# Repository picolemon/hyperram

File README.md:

# HyperRAM PMOD :lemon: # 

### Overview :hammer:
HyperRam board for use with PMOD compatible FPGA devices. This repo contains the
example RTL code, datasheets and schematics for the device.

### Whats included :musical_note:
- [x] Example wishbone memory controller.
- [x] Memory tester to validate the device works.
- [x] [Schematic](doc/sch.pdf), [PCB](pcb/) and [BOM](https://htmlpreview.github.io/?https://github.com/picolemon/hyperram/blob/main/doc/ibom.html).

### Getting started :mag:
Read the [datasheet](doc/datasheet.pdf) and run the [example](examples/) project.

### Support :zap:
- Drop by the [discord](https://discord.gg/Be3yFCzyrp)
- Email help@picolemon.com

### License :penguin:
 
The MIT License (MIT)

Copyright (c) 2023 picoLemon

Permission is hereby granted, free of charge, to any person obtaining a copy of this software and associated documentation files (the "Software"), to deal in the Software without restriction, including without limitation the rights to use, copy, modify, merge, publish, distribute, sublicense, and/or sell copies of the Software, and to permit persons to whom the Software is furnished to do so, subject to the following conditions:

The above copyright notice and this permission notice shall be included in all copies or substantial portions of the Software.

THE SOFTWARE IS PROVIDED "AS IS", WITHOUT WARRANTY OF ANY KIND, EXPRESS OR IMPLIED, INCLUDING BUT NOT LIMITED TO THE WARRANTIES OF MERCHANTABILITY, FITNESS FOR A PARTICULAR PURPOSE AND NONINFRINGEMENT. IN NO EVENT SHALL THE AUTHORS OR COPYRIGHT HOLDERS BE LIABLE FOR ANY CLAIM, DAMAGES OR OTHER LIABILITY, WHETHER IN AN ACTION OF CONTRACT, TORT OR OTHERWISE, ARISING FROM, OUT OF OR IN CONNECTION WITH THE SOFTWARE OR THE USE OR OTHER DEALINGS IN THE SOFTWARE.

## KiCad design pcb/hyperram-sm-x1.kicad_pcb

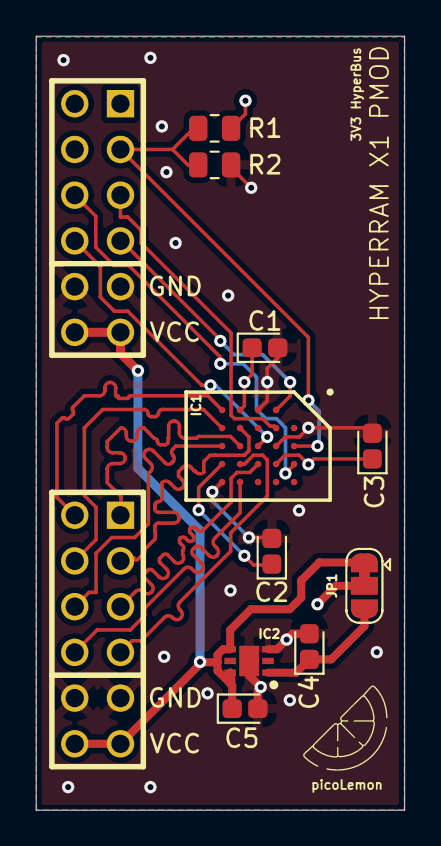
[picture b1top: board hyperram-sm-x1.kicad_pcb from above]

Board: 4 copper layers, 20.5 x 43.0 mm, 12 parts (0 on the bottom side), 17 nets.

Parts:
C1, C2, C3: 100n; CP_EIA-1608-08_AVX-J
C4, C5: 1u; CP_EIA-1608-08_AVX-J
IC1: W957A8MFYA5I; BGA24C100P5X5_600X800X120
IC2: NCP705MT18TCG; SON65P200X200X80-7N
J1, J2: PMOD; pmod_pin_array_6x2
JP1: VCC_3V_SEL; SolderJumper-3_P1.3mm_Bridged23_RoundedPad1.0x1.5mm
R1, R2: 8k; R_0805_2012Metric

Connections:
+1V8: C4.1, IC2.1 (OUT), JP1.1 (A)
+3V3: C5.1, IC2.4 (EN), IC2.6 (IN), J1.6, J1.12, J2.6, J2.12, JP1.3 (B)
/DQ0: IC1.D3 (DQ0), J2.1
/DQ1: IC1.D2 (DQ1), J2.2
/DQ2: IC1.C4 (DQ2), J2.3
/DQ3: IC1.D4 (DQ3), J2.4
/DQ4: IC1.D5 (DQ4), J2.10
/DQ5: IC1.E3 (DQ5), J2.9
/DQ6: IC1.E2 (DQ6), J2.8
/DQ7: IC1.E1 (DQ7), J2.7
CK: IC1.B2 (CK), J1.3
GND: C1.2, C2.2, C3.2, C4.2, C5.2, IC1.B3 (VSS), IC1.C1 (VSSQ_1), IC1.E5 (VSSQ_2), IC2.3 (GND_1), IC2.7 (GND_2), J1.5, J1.11, J2.5, J2.11, R2.2
RWDS: IC1.C3 (RWDS), J1.10
VCC: C1.1, C2.1, C3.1, IC1.B4 (VCC), IC1.D1 (VCCQ_1), IC1.E4 (VCCQ_2), JP1.2 (C), R1.1
~CK: IC1.B1 (CK#), J1.4
~CS0: IC1.A3 (CS#), J1.2, R1.2, R2.1
~RESET: IC1.A4 (RESET#), J1.9

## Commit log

2023-03-28 Base commit
